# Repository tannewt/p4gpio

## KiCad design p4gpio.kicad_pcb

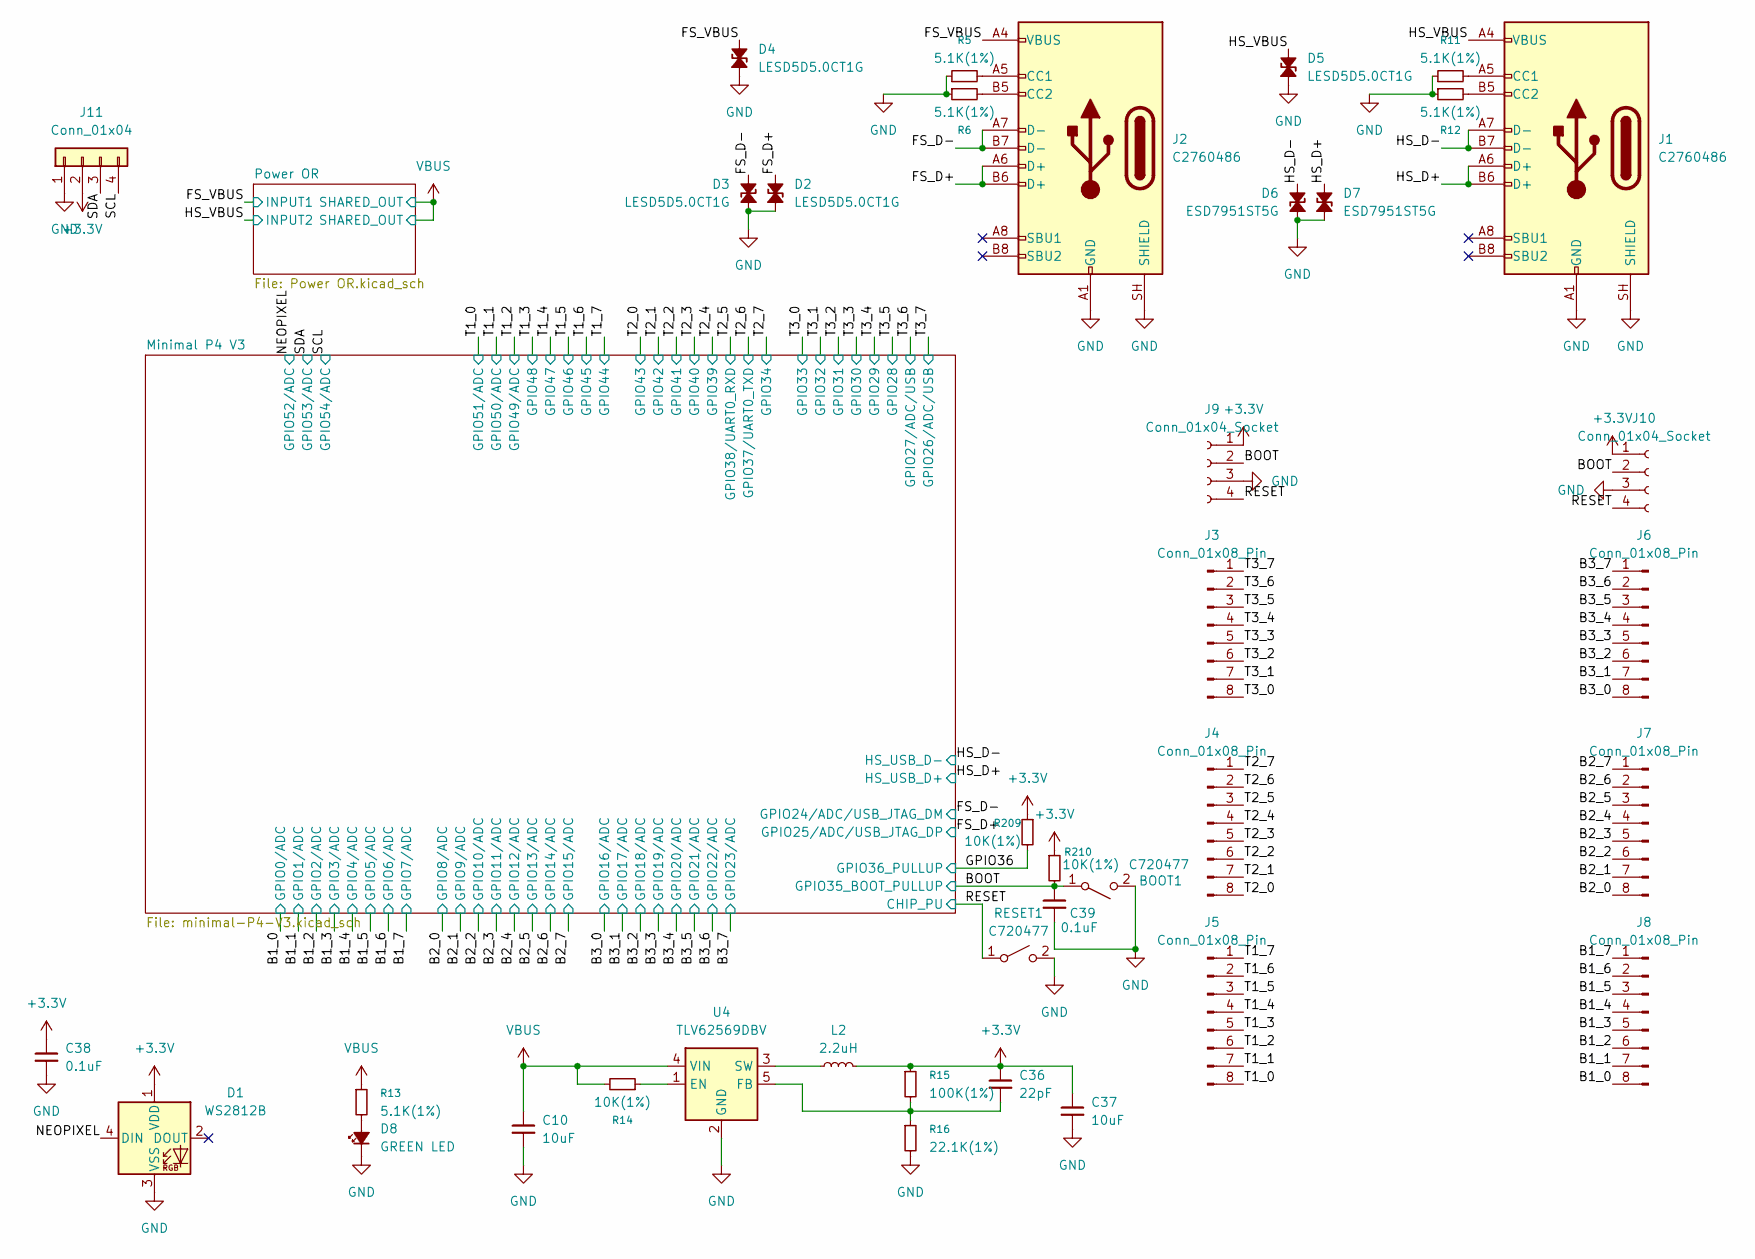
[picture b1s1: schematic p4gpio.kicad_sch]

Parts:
BOOT1: C720477; SW_SPST_TS-1088-xR020
C10, C37: 10uF; C_0603_1608Metric
C36: 22pF; C_0402_1005Metric
C38, C39: 0.1uF; C_0402_1005Metric
D1: WS2812B; LED_WS2812B_PLCC4_5.0x5.0mm_P3.2mm
D2, D3, D4, D5: LESD5D5.0CT1G; D_SOD-523
D6, D7: ESD7951ST5G; D_SOD-882
D8: GREEN LED; D_0805_2012Metric
J1, J2: C2760486; USB_C_Receptacle_HRO_TYPE-C-31-M-31
J3, J4, J5, J6, J7, J8: Conn_01x08_Pin; PinHeader_1x08_P2.54mm_Vertical
J9, J10: Conn_01x04_Socket; PinSocket_1x04_P2.54mm_Vertical
J11: Conn_01x04; JST_SH_SM04B-SRSS-TB_1x04-1MP_P1.00mm_Horizontal
L2: 2.2uH; L_1008_2520Metric
R5, R6, R11, R12, R13: 5.1K(1%); R_0402_1005Metric
R14, R209, R210: 10K(1%); R_0402_1005Metric
R15: 100K(1%); R_0402_1005Metric
R16: 22.1K(1%); R_0402_1005Metric
RESET1: C720477; SW_SPST_TS-1088-xR020
U4: TLV62569DBV; SOT-23-5

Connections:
+3.3V: C36.1, C37.1, C38.1, D1.1 (VDD), J9.1, J10.1, J11.2, L2.2, R15.1, R209.1, R210.1; also elsewhere on the board
/B1_0: J8.8; also elsewhere on the board
/B1_1: J8.7; also elsewhere on the board
/B1_2: J8.6; also elsewhere on the board
/B1_3: J8.5; also elsewhere on the board
/B1_4: J8.4; also elsewhere on the board
/B1_5: J8.3; also elsewhere on the board
/B1_6: J8.2; also elsewhere on the board
/B1_7: J8.1; also elsewhere on the board
/B2_0: J7.8; also elsewhere on the board
/B2_1: J7.7; also elsewhere on the board
/B2_2: J7.6; also elsewhere on the board
/B2_3: J7.5; also elsewhere on the board
/B2_4: J7.4; also elsewhere on the board
/B2_5: J7.3; also elsewhere on the board
/B2_6: J7.2; also elsewhere on the board
/B2_7: J7.1; also elsewhere on the board
/B3_0: J6.8; also elsewhere on the board
/B3_1: J6.7; also elsewhere on the board
/B3_2: J6.6; also elsewhere on the board
/B3_3: J6.5; also elsewhere on the board
/B3_4: J6.4; also elsewhere on the board
/B3_5: J6.3; also elsewhere on the board
/B3_6: J6.2; also elsewhere on the board
/B3_7: J6.1; also elsewhere on the board
/BOOT: BOOT1.1 (A), C39.1, J9.2, J10.2, R210.2; also elsewhere on the board
/FS_D+: D2.2 (A2), J2.A6 (D+), J2.B6 (D+); also elsewhere on the board
/FS_D-: D3.2 (A2), J2.A7 (D-), J2.B7 (D-); also elsewhere on the board
/FS_VBUS: D4.2 (A2), J2.A4 (VBUS), J2.A9 (VBUS), J2.B4 (VBUS), J2.B9 (VBUS); also elsewhere on the board
/GPIO36: R209.2; also elsewhere on the board
/HS_D+: D7.2 (A2), J1.A6 (D+), J1.B6 (D+); also elsewhere on the board
/HS_D-: D6.2 (A2), J1.A7 (D-), J1.B7 (D-); also elsewhere on the board
/HS_VBUS: D5.2 (A2), J1.A4 (VBUS), J1.A9 (VBUS), J1.B4 (VBUS), J1.B9 (VBUS); also elsewhere on the board
/NEOPIXEL: D1.4 (DIN); also elsewhere on the board
/RESET: J9.4, J10.4, RESET1.1 (A); also elsewhere on the board
/SCL: J11.4; also elsewhere on the board
/SDA: J11.3; also elsewhere on the board
/T1_0: J5.8; also elsewhere on the board
/T1_1: J5.7; also elsewhere on the board
/T1_2: J5.6; also elsewhere on the board
/T1_3: J5.5; also elsewhere on the board
/T1_4: J5.4; also elsewhere on the board
/T1_5: J5.3; also elsewhere on the board
/T1_6: J5.2; also elsewhere on the board
/T1_7: J5.1; also elsewhere on the board
/T2_0: J4.8; also elsewhere on the board
/T2_1: J4.7; also elsewhere on the board
/T2_2: J4.6; also elsewhere on the board
/T2_3: J4.5; also elsewhere on the board
/T2_4: J4.4; also elsewhere on the board
/T2_5: J4.3; also elsewhere on the board
/T2_6: J4.2; also elsewhere on the board
/T2_7: J4.1; also elsewhere on the board
/T3_0: J3.8; also elsewhere on the board
/T3_1: J3.7; also elsewhere on the board
/T3_2: J3.6; also elsewhere on the board
/T3_3: J3.5; also elsewhere on the board
/T3_4: J3.4; also elsewhere on the board
/T3_5: J3.3; also elsewhere on the board
/T3_6: J3.2; also elsewhere on the board
/T3_7: J3.1; also elsewhere on the board
GND: BOOT1.2 (B), C10.2, C37.2, C38.2, C39.2, D1.3 (VSS), D2.1 (A1), D3.1 (A1), D4.1 (A1), D5.1 (A1), D6.1 (A1), D7.1 (A1), D8.1 (K), J1.A1 (GND), J1.A12 (GND), J1.B1 (GND), J1.B12 (GND), J1.SH (SHIELD), J2.A1 (GND), J2.A12 (GND), J2.B1 (GND), J2.B12 (GND), J2.SH (SHIELD), J9.3, J10.3, J11.1, R5.1, R6.1, R11.1, R12.1, R16.2, RESET1.2 (B), U4.2 (GND); also elsewhere on the board
unnamed: D8.2 (A), R13.2
unnamed: J1.A5 (CC1), R11.2
unnamed: J1.B5 (CC2), R12.2
unnamed: J2.A5 (CC1), R5.2
unnamed: J2.B5 (CC2), R6.2
unnamed: R14.1, U4.1 (EN)
unnamed: C36.2, R15.2, R16.1, U4.5 (FB)
unnamed: L2.1, U4.3 (SW)
VBUS: C10.1, R13.1, R14.2, U4.4 (VIN); also elsewhere on the board

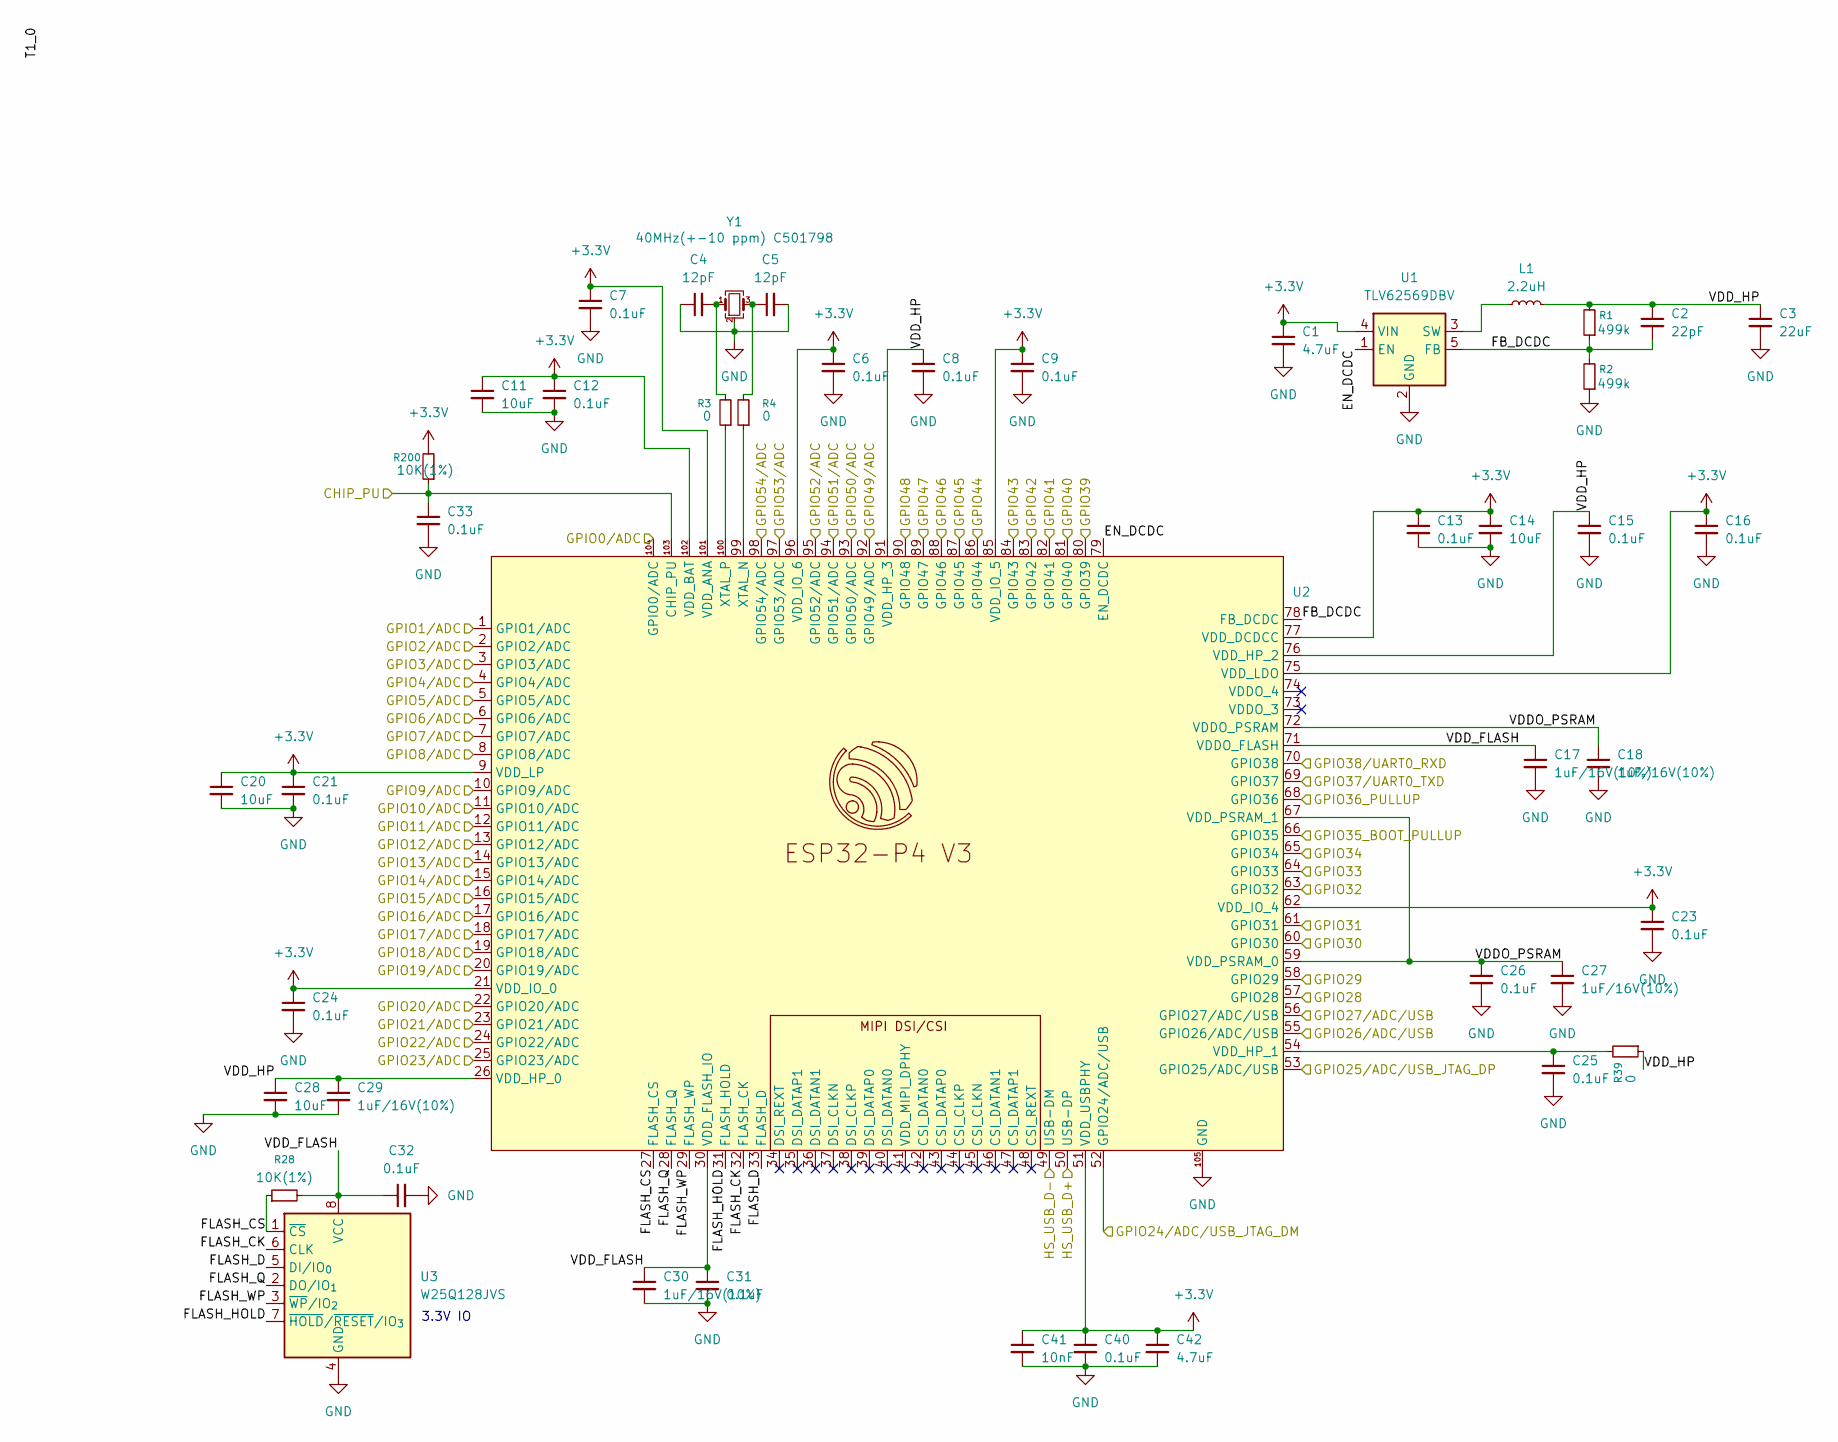
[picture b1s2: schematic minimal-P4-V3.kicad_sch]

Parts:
C1, C42: 4.7uF; C_0402_1005Metric
C2: 22pF; C_0402_1005Metric
C3: 22uF; C_0603_1608Metric
C4, C5: 12pF; C_0402_1005Metric
C6, C7, C8, C9, C12, C13, C15, C16, C21, C23, C24, C25, C26, C31, C32, C33, C40: 0.1uF; C_0402_1005Metric
C11, C14, C20, C28: 10uF; C_0603_1608Metric
C17, C18, C27, C29, C30: 1uF/16V(10%); C_0402_1005Metric
C41: 10nF; C_0402_1005Metric
L1: 2.2uH; L_1008_2520Metric
R1, R2: 499k; R_0402_1005Metric
R3, R4, R39: 0; R_0402_1005Metric
R28, R200: 10K(1%); R_0402_1005Metric
U1: TLV62569DBV; SOT-23-5
U2: ESP32-P4
U3: W25Q128JVS; WSON-8-1EP_6x5mm_P1.27mm_EP3.4x4.3mm
Y1: 40MHz(+-10 ppm) C501798; Crystal_SMD_2016-4Pin_2.0x1.6mm

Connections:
+3.3V: C1.1, C6.1, C7.1, C9.1, C11.1, C12.1, C13.1, C14.1, C16.1, C20.1, C21.1, C23.1, C24.1, C40.1, C41.1, C42.1, R200.2, U1.4 (VIN), U2.9 (VDD_LP), U2.21 (VDD_IO_0), U2.51 (VDD_USBPHY), U2.62 (VDD_IO_4), U2.75 (VDD_LDO), U2.77 (VDD_DCDCC), U2.85 (VDD_IO_5), U2.96 (VDD_IO_6), U2.101 (VDD_ANA), U2.102 (VDD_BAT); also elsewhere on the board
/B1_0: U2.104 (GPIO0/ADC); also elsewhere on the board
/B1_1: U2.1 (GPIO1/ADC); also elsewhere on the board
/B1_2: U2.2 (GPIO2/ADC); also elsewhere on the board
/B1_3: U2.3 (GPIO3/ADC); also elsewhere on the board
/B1_4: U2.4 (GPIO4/ADC); also elsewhere on the board
/B1_5: U2.5 (GPIO5/ADC); also elsewhere on the board
/B1_6: U2.6 (GPIO6/ADC); also elsewhere on the board
/B1_7: U2.7 (GPIO7/ADC); also elsewhere on the board
/B2_0: U2.8 (GPIO8/ADC); also elsewhere on the board
/B2_1: U2.10 (GPIO9/ADC); also elsewhere on the board
/B2_2: U2.11 (GPIO10/ADC); also elsewhere on the board
/B2_3: U2.12 (GPIO11/ADC); also elsewhere on the board
/B2_4: U2.13 (GPIO12/ADC); also elsewhere on the board
/B2_5: U2.14 (GPIO13/ADC); also elsewhere on the board
/B2_6: U2.15 (GPIO14/ADC); also elsewhere on the board
/B2_7: U2.16 (GPIO15/ADC); also elsewhere on the board
/B3_0: U2.17 (GPIO16/ADC); also elsewhere on the board
/B3_1: U2.18 (GPIO17/ADC); also elsewhere on the board
/B3_2: U2.19 (GPIO18/ADC); also elsewhere on the board
/B3_3: U2.20 (GPIO19/ADC); also elsewhere on the board
/B3_4: U2.22 (GPIO20/ADC); also elsewhere on the board
/B3_5: U2.23 (GPIO21/ADC); also elsewhere on the board
/B3_6: U2.24 (GPIO22/ADC); also elsewhere on the board
/B3_7: U2.25 (GPIO23/ADC); also elsewhere on the board
/BOOT: U2.66 (GPIO35); also elsewhere on the board
/FS_D+: U2.53 (GPIO25/ADC/USB); also elsewhere on the board
/FS_D-: U2.52 (GPIO24/ADC/USB); also elsewhere on the board
/GPIO36: U2.68 (GPIO36); also elsewhere on the board
/HS_D+: U2.50 (USB-DP); also elsewhere on the board
/HS_D-: U2.49 (USB-DM); also elsewhere on the board
/Minimal P4 V3/EN_DCDC: U1.1 (EN), U2.79 (EN_DCDC)
/Minimal P4 V3/FB_DCDC: C2.2, R1.1, R2.2, U1.5 (FB), U2.78 (FB_DCDC)
/Minimal P4 V3/FLASH_CK: U2.32 (FLASH_CK), U3.6 (CLK)
/Minimal P4 V3/FLASH_CS: R28.1, U2.27 (FLASH_CS), U3.1 (~CS)
/Minimal P4 V3/FLASH_D: U2.33 (FLASH_D), U3.5 (DI/IO_{0})
/Minimal P4 V3/FLASH_HOLD: U2.31 (FLASH_HOLD), U3.7 (~HOLD/~RESET/IO_{3})
/Minimal P4 V3/FLASH_Q: U2.28 (FLASH_Q), U3.2 (DO/IO_{1})
/Minimal P4 V3/FLASH_WP: U2.29 (FLASH_WP), U3.3 (~WP/IO_{2})
/Minimal P4 V3/VDDO_PSRAM: C18.1, C26.1, C27.1, U2.59 (VDD_PSRAM_0), U2.67 (VDD_PSRAM_1), U2.72 (VDDO_PSRAM)
/Minimal P4 V3/VDD_FLASH: C17.1, C30.1, C31.1, C32.1, R28.2, U2.30 (VDD_FLASH_IO), U2.71 (VDDO_FLASH), U3.8 (VCC)
/Minimal P4 V3/VDD_HP: C2.1, C3.1, C8.1, C15.1, C28.1, C29.1, L1.2, R1.2, R39.1, U2.26 (VDD_HP_0), U2.76 (VDD_HP_2), U2.91 (VDD_HP_3)
/NEOPIXEL: U2.95 (GPIO52/ADC); also elsewhere on the board
/RESET: C33.1, R200.1, U2.103 (CHIP_PU); also elsewhere on the board
/SCL: U2.98 (GPIO54/ADC); also elsewhere on the board
/SDA: U2.97 (GPIO53/ADC); also elsewhere on the board
/T1_0: U2.94 (GPIO51/ADC); also elsewhere on the board
/T1_1: U2.93 (GPIO50/ADC); also elsewhere on the board
/T1_2: U2.92 (GPIO49/ADC); also elsewhere on the board
/T1_3: U2.90 (GPIO48); also elsewhere on the board
/T1_4: U2.89 (GPIO47); also elsewhere on the board
/T1_5: U2.88 (GPIO46); also elsewhere on the board
/T1_6: U2.87 (GPIO45); also elsewhere on the board
/T1_7: U2.86 (GPIO44); also elsewhere on the board
/T2_0: U2.84 (GPIO43); also elsewhere on the board
/T2_1: U2.83 (GPIO42); also elsewhere on the board
/T2_2: U2.82 (GPIO41); also elsewhere on the board
/T2_3: U2.81 (GPIO40); also elsewhere on the board
/T2_4: U2.80 (GPIO39); also elsewhere on the board
/T2_5: U2.70 (GPIO38); also elsewhere on the board
/T2_6: U2.69 (GPIO37); also elsewhere on the board
/T2_7: U2.65 (GPIO34); also elsewhere on the board
/T3_0: U2.64 (GPIO33); also elsewhere on the board
/T3_1: U2.63 (GPIO32); also elsewhere on the board
/T3_2: U2.61 (GPIO31); also elsewhere on the board
/T3_3: U2.60 (GPIO30); also elsewhere on the board
/T3_4: U2.58 (GPIO29); also elsewhere on the board
/T3_5: U2.57 (GPIO28); also elsewhere on the board
/T3_6: U2.56 (GPIO27/ADC/USB); also elsewhere on the board
/T3_7: U2.55 (GPIO26/ADC/USB); also elsewhere on the board
GND: C1.2, C3.2, C4.1, C5.2, C6.2, C7.2, C8.2, C9.2, C11.2, C12.2, C13.2, C14.2, C15.2, C16.2, C17.2, C18.2, C20.2, C21.2, C23.2, C24.2, C25.2, C26.2, C27.2, C28.2, C29.2, C30.2, C31.2, C32.2, C33.2, C40.2, C41.2, C42.2, R2.1, U1.2 (GND), U2.105 (GND), U3.4 (GND), Y1.2 (G), Y1.4 (G); also elsewhere on the board
unnamed: C4.2, R3.2, Y1.1
unnamed: C5.1, R4.2, Y1.3
unnamed: L1.1, U1.3 (SW)
unnamed: C25.1, R39.2, U2.54 (VDD_HP_1)
unnamed: R4.1, U2.99 (XTAL_N)
unnamed: R3.1, U2.100 (XTAL_P)

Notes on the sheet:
3.3V IO

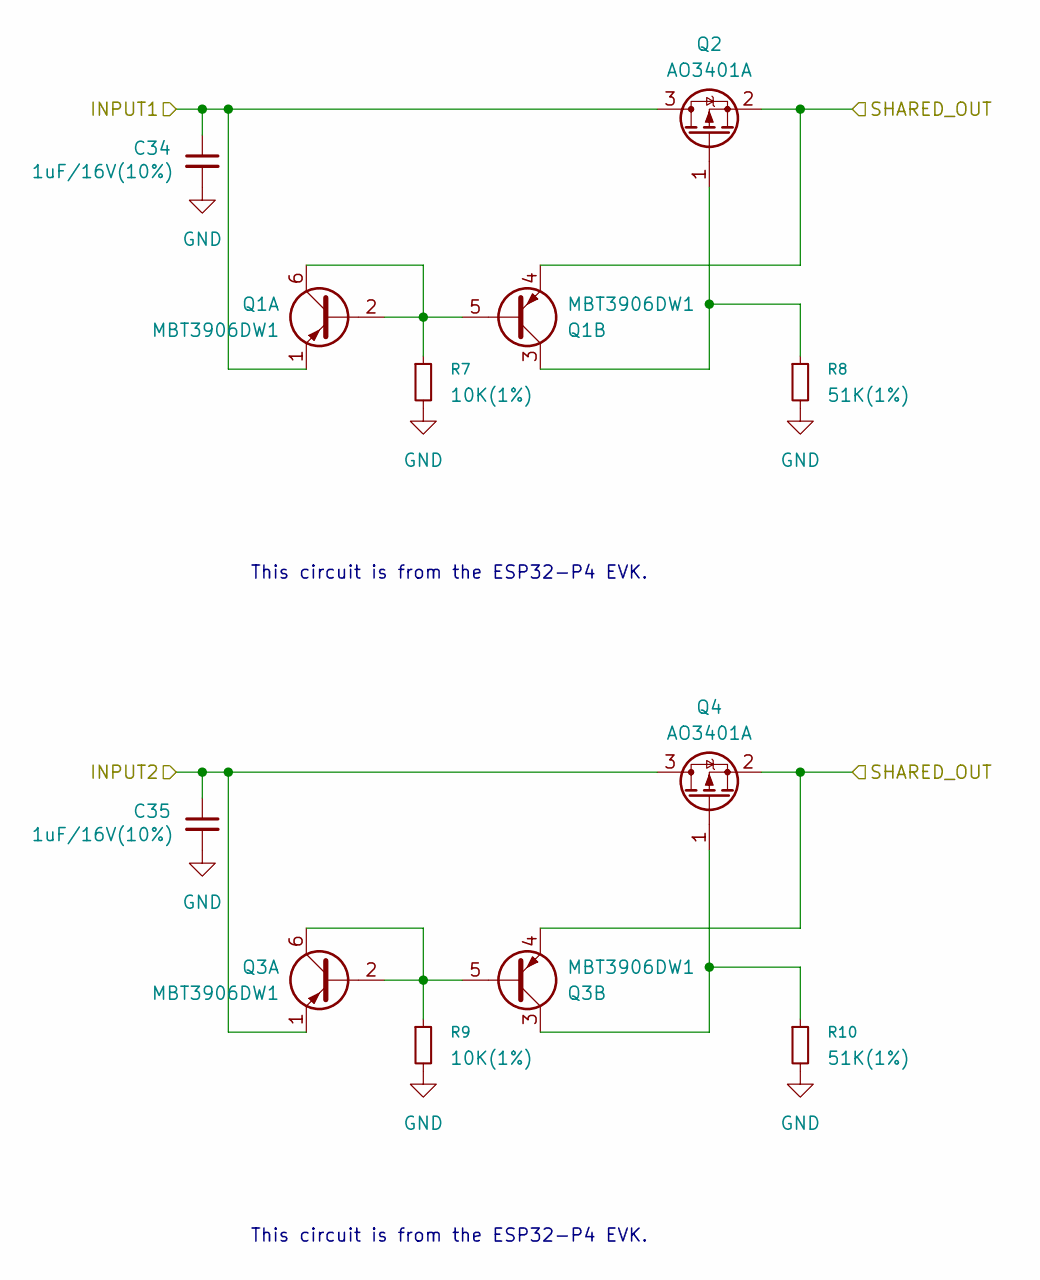
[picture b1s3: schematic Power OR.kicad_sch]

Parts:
C34, C35: 1uF/16V(10%); C_0402_1005Metric
Q1, Q3: MBT3906DW1; SOT-363_SC-70-6
Q2, Q4: AO3401A; SOT-23
R7, R9: 10K(1%); R_0402_1005Metric
R8, R10: 51K(1%); R_0402_1005Metric

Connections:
/FS_VBUS: C34.1, Q1.1 (E1), Q2.3 (D); also elsewhere on the board
/HS_VBUS: C35.1, Q3.1 (E1), Q4.3 (D); also elsewhere on the board
GND: C34.2, C35.2, R7.2, R8.2, R9.2, R10.2; also elsewhere on the board
unnamed: Q1.2 (B1), Q1.5 (B2), Q1.6 (C1), R7.1
unnamed: Q1.3 (C2), Q2.1 (G), R8.1
unnamed: Q3.2 (B1), Q3.5 (B2), Q3.6 (C1), R9.1
unnamed: Q3.3 (C2), Q4.1 (G), R10.1
VBUS: Q1.4 (E2), Q2.2 (S), Q3.4 (E2), Q4.2 (S); also elsewhere on the board

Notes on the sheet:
This circuit is from the ESP32-P4 EVK.

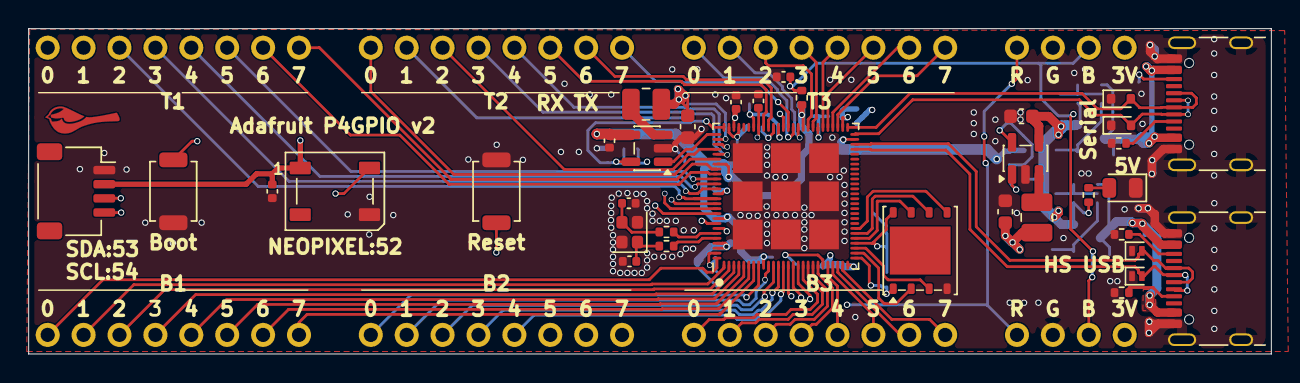
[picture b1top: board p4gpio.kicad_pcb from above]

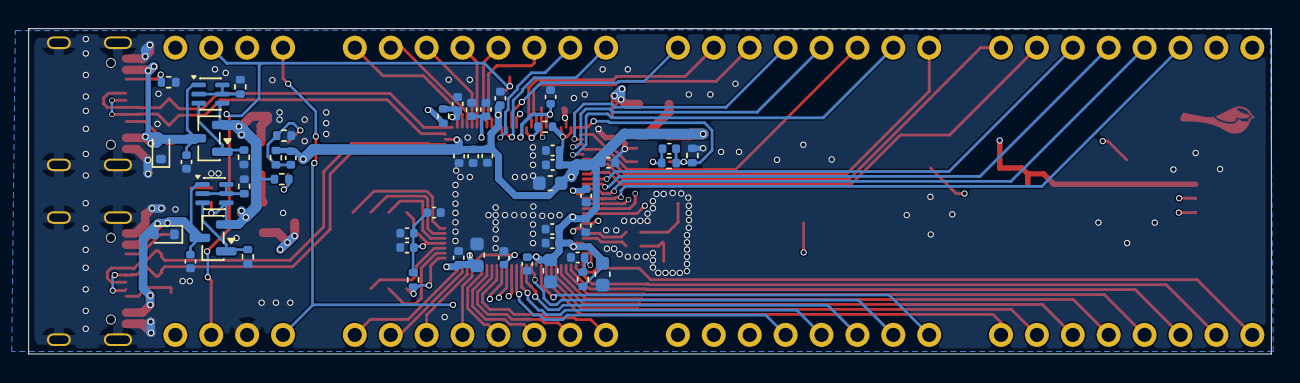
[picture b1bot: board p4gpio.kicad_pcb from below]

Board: 4 copper layers, 87.9 x 23.0 mm, 93 parts (56 on the bottom side), 92 nets.

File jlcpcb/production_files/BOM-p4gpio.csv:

Comment,Designator,Footprint,LCSC,Quantity
0,"R3,R39,R4",R_0402_1005Metric,C17168,3
0.1uF,"C12,C13,C15,C16,C21,C23,C24,C25,C26,C31,C32,C33,C38,C39,C40,C6,C7,C8,C9",C_0402_1005Metric,C1525,19
100K(1%),R15,R_0402_1005Metric,C25741,1
10K(1%),"R14,R200,R209,R210,R28,R7,R9",R_0402_1005Metric,C25744,7
10nF,C41,C_0402_1005Metric,C15195,1
10uF,"C10,C11,C14,C20,C28,C37",C_0603_1608Metric,C19702,6
12pF,"C4,C5",C_0402_1005Metric,C1547,2
1uF/16V(10%),"C17,C18,C27,C29,C30,C34,C35",C_0402_1005Metric,C52923,7
2.2uH,"L1,L2",L_1008_2520Metric,C279858,2
22.1K(1%),R16,R_0402_1005Metric,C2929993,1
22pF,"C2,C36",C_0402_1005Metric,C1555,2
22uF,C3,C_0603_1608Metric,C59461,1
4.7uF,"C1,C42",C_0402_1005Metric,C23733,2
40MHz(+-10 ppm) C501798,Y1,Crystal_SMD_2016-4Pin_2.0x1.6mm,C501798,1
499k,"R1,R2",R_0402_1005Metric,C137971,2
5.1K(1%),"R11,R12,R13,R5,R6",R_0402_1005Metric,C25905,5
51K(1%),"R10,R8",R_0402_1005Metric,C25794,2
AO3401A,"Q2,Q4",SOT-23,C15127,2
C2760486,"J1,J2",USB_C_Receptacle_HRO_TYPE-C-31-M-31,C2760486,2
C720477,"BOOT1,RESET1",SW_SPST_TS-1088-xR020,C720477,2
Conn_01x04,J11,JST_SH_SM04B-SRSS-TB_1x04-1MP_P1.00mm_Horizontal,C160404,1
ESD7951ST5G,"D6,D7",D_SOD-882,C343992,2
GREEN LED,D8,D_0805_2012Metric,C2297,1
LESD5D5.0CT1G,"D2,D3,D4,D5",D_SOD-523,C5274290,4
MBT3906DW1,"Q1,Q3",SOT-363_SC-70-6,C13962,2
TLV62569DBV,"U1,U4",SOT-23-5,C141836,2
W25Q128JVS,U3,WSON-8-1EP_6x5mm_P1.27mm_EP3.4x4.3mm,C190862,1
WS2812B,D1,LED_WS2812B_PLCC4_5.0x5.0mm_P3.2mm,C2874885,1
~,U2,ESP32-P4,C22387510,1

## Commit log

2026-04-16 Initial version of minimal ESP32-P4 dev board
    (Core schematic done in preparation for design blockification)
2026-04-18 Start work on layout
2026-04-20 Schematic done except for GPIO
2026-04-20 Setup design rules. Start to match up pins
2026-04-21 Lots more routing and placement
2026-04-21 More power routing
2026-04-22 more routing
2026-04-22 Fix bootstrapping pins. Start fixing DRC
2026-04-22 Done?
2026-04-23 Prep to order. Need to make vias bigger
2026-04-23 Ordered
2026-05-07 Connect flash VDD and skooch USBs apart. Start of v2
2026-05-07 ready for v2
2026-05-08 Fix design block import
2026-05-11 Add bom and cpl
